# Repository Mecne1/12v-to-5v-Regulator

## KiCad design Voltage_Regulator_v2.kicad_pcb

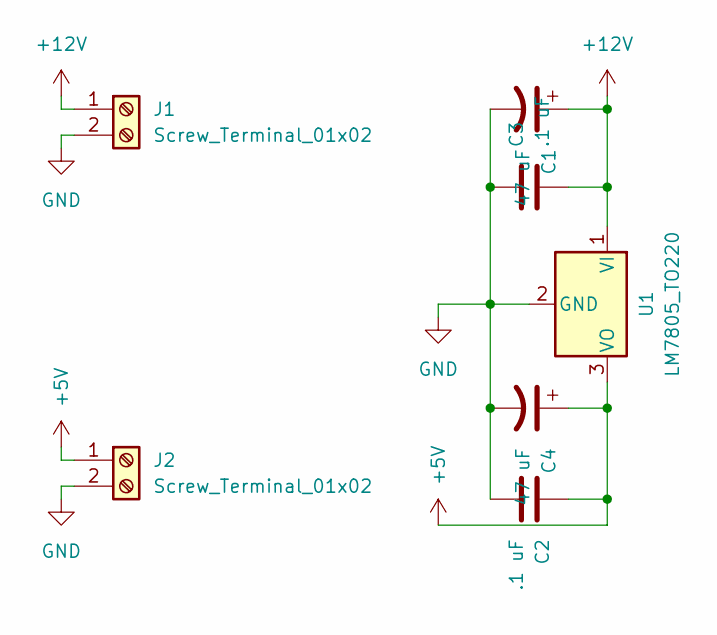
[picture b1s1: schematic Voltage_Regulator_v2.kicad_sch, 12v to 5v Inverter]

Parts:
C1, C4: 47 uF; CP_Radial_D5.0mm_P2.00mm
C2, C3: .1 uF; C_0805_2012Metric
J1, J2: Screw_Terminal_01x02; TerminalBlock_4Ucon_1x02_P3.50mm_Vertical
U1: LM7805_TO220; TO-220-3_Vertical

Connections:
+5V: C2.1, C4.1, J2.1, U1.3 (VO)
+12V: C1.1, C3.2, J1.1, U1.1 (VI)
GND: C1.2, C2.2, C3.1, C4.2, J1.2, J2.2, U1.2 (GND)

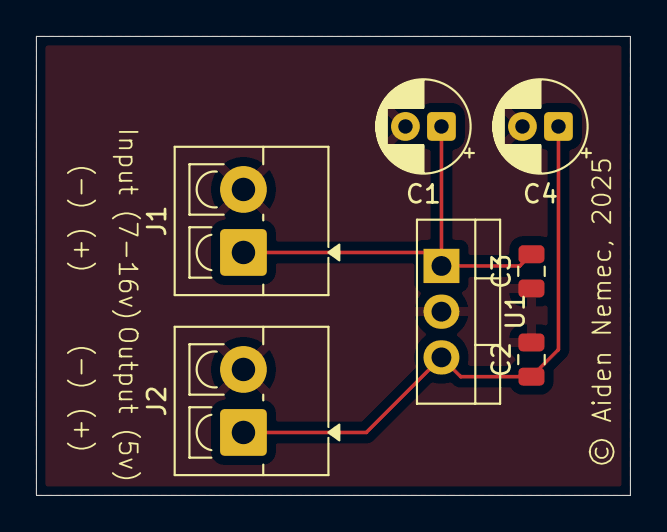
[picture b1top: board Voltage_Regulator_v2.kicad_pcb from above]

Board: 2 copper layers, 33.0 x 25.5 mm, 7 parts (0 on the bottom side), 3 nets.

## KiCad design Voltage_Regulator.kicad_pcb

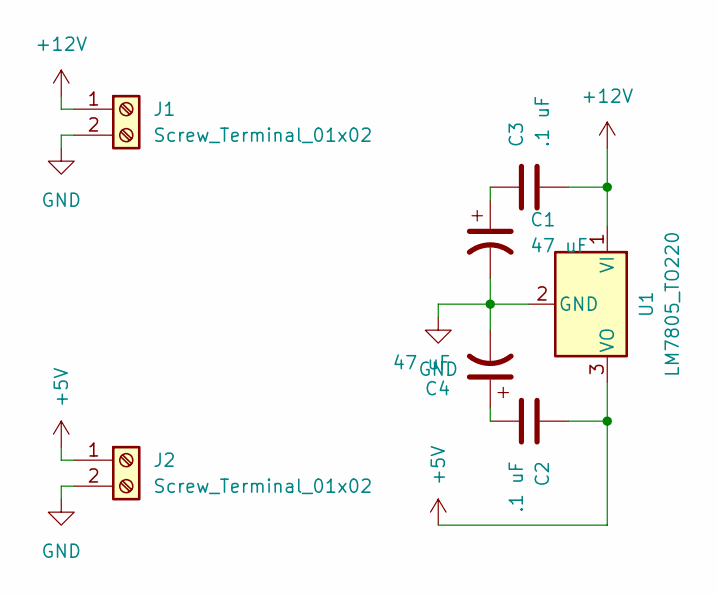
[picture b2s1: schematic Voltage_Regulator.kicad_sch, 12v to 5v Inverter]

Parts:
C1, C4: 47 uF; CP_Radial_D5.0mm_P2.00mm
C2, C3: .1 uF; C_0805_2012Metric
J1, J2: Screw_Terminal_01x02; TerminalBlock_4Ucon_1x02_P3.50mm_Vertical
U1: LM7805_TO220; TO-220-3_Vertical

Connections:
+5V: C2.1, J2.1, U1.3 (VO)
+12V: C3.2, J1.1, U1.1 (VI)
GND: C1.2, C4.2, J1.2, J2.2, U1.2 (GND)
unnamed: C1.1, C3.1
unnamed: C2.2, C4.1

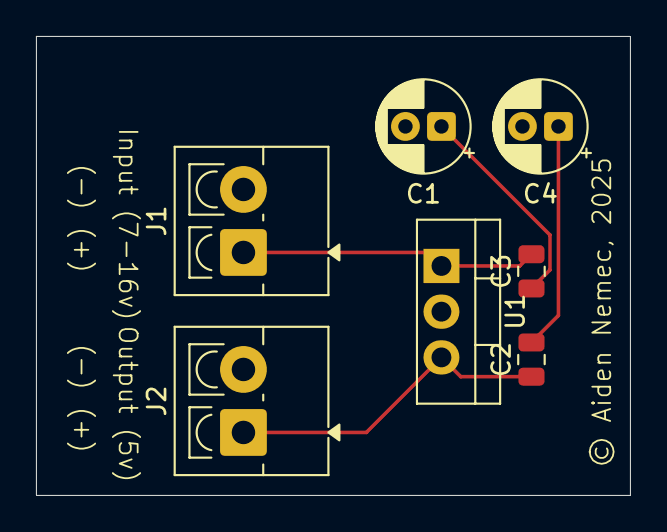
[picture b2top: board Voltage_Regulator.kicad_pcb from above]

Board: 2 copper layers, 33.0 x 25.5 mm, 7 parts (0 on the bottom side), 5 nets.

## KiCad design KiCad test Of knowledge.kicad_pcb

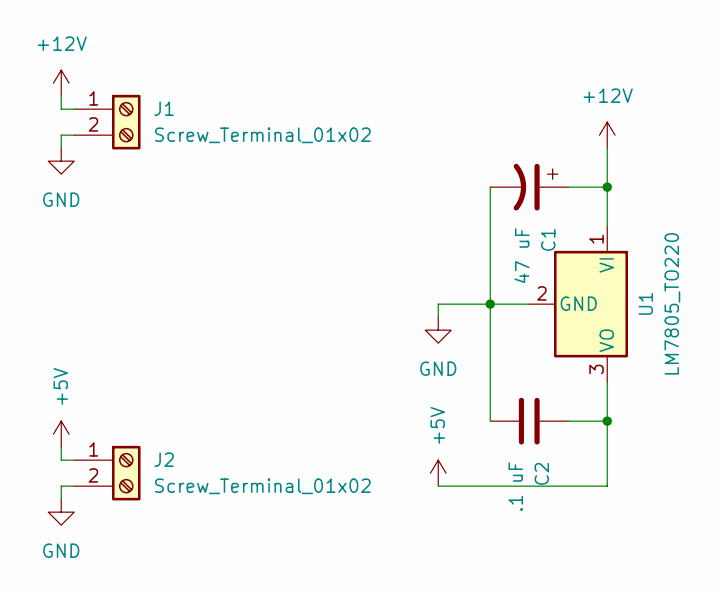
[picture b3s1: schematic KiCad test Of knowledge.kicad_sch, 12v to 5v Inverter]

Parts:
C1: 47 uF; CP_Radial_D30.0mm_P10.00mm_SnapIn
C2: .1 uF; C_0805_2012Metric
J1, J2: Screw_Terminal_01x02; TerminalBlock_4Ucon_1x02_P3.50mm_Vertical
U1: LM7805_TO220; TO-220-3_Vertical

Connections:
+5V: C2.1, J2.1, U1.3 (VO)
+12V: C1.1, J1.1, U1.1 (VI)
GND: C1.2, C2.2, J1.2, J2.2, U1.2 (GND)

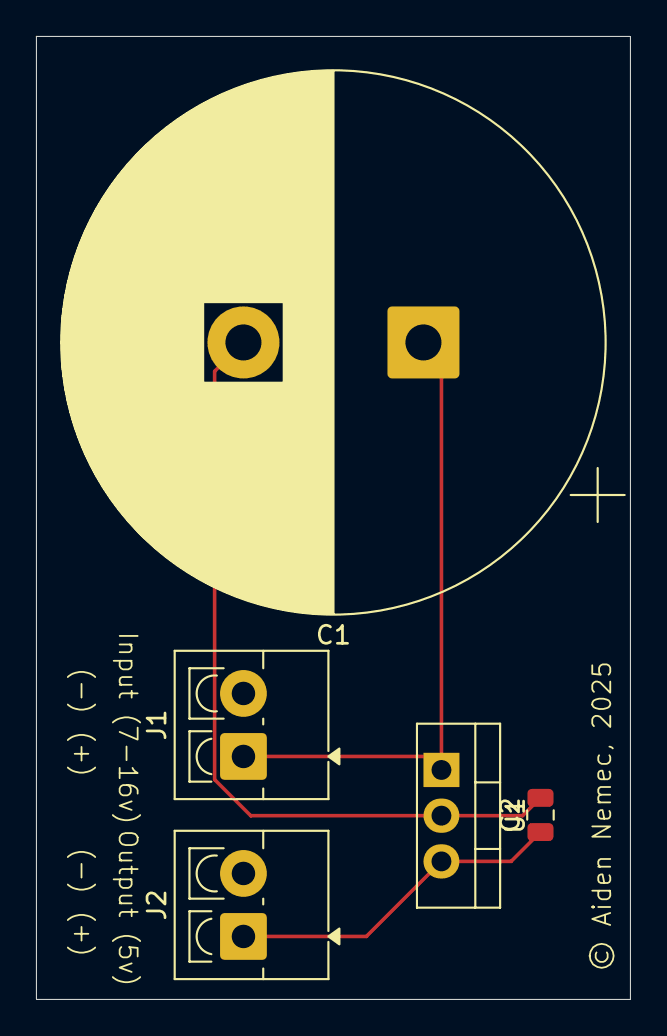
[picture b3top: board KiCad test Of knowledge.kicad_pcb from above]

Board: 2 copper layers, 33.0 x 53.5 mm, 5 parts (0 on the bottom side), 3 nets.

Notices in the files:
KiCad test Of knowledge.kicad_pcb:
© Aiden Nemec, 2025
KiCad test Of knowledge.kicad_sch:
©2025, Aiden Nemec.
